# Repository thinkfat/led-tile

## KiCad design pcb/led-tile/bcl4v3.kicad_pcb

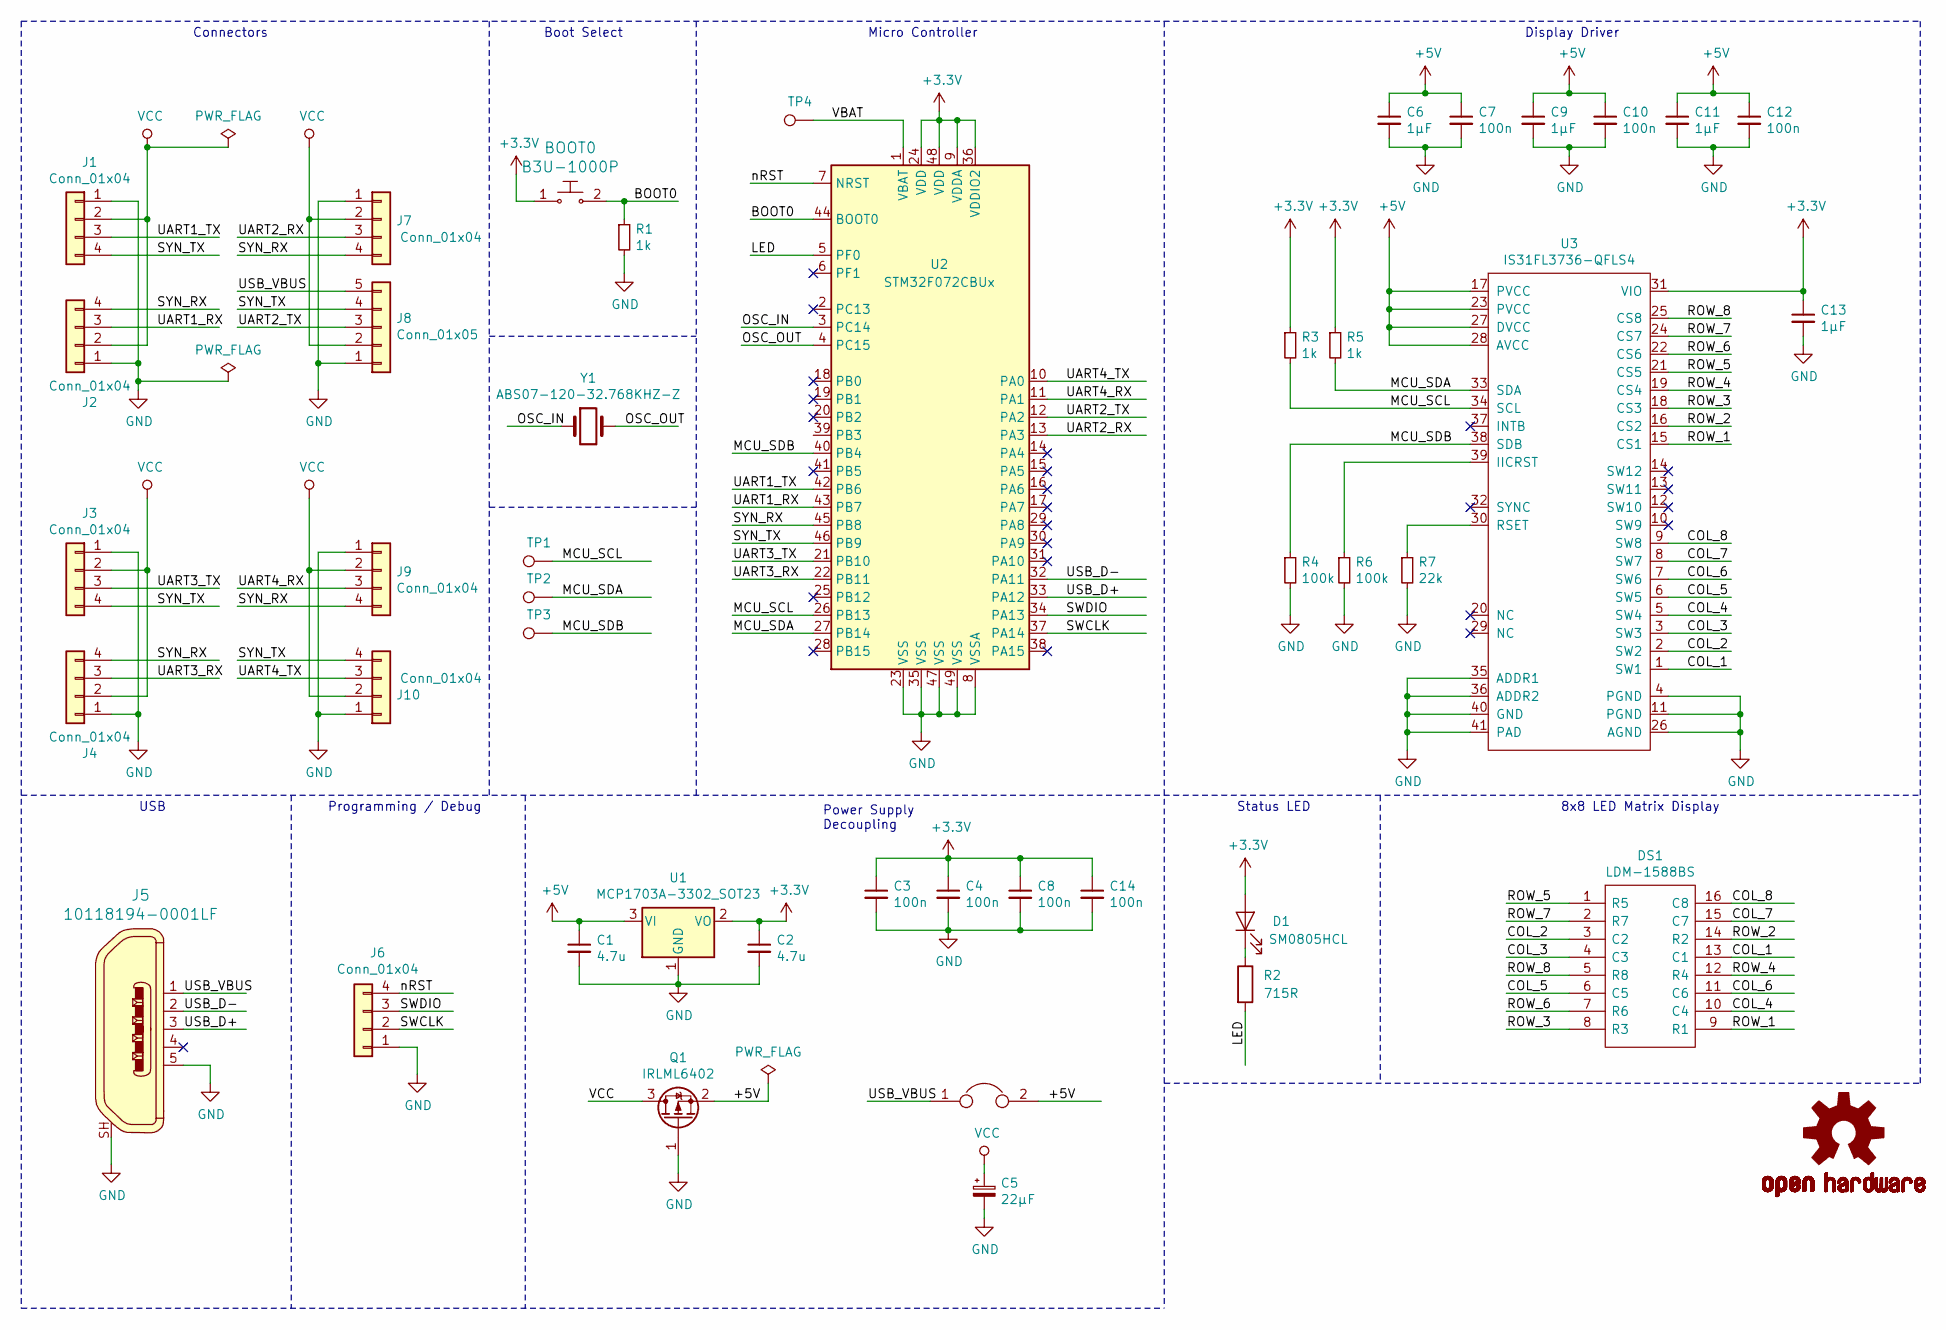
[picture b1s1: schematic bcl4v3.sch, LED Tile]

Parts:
BOOT0: B3U-1000P; Switch_Tactile_SMD_B3U-1000P; MPN B3U-1000P; Digi-Key_PN SW1020CT-ND
C1, C2: 4.7u; C_0805_2012Metric_Pad1.15x1.40mm_HandSolder
C3, C4, C7, C8, C10, C12, C14: 100n; C_0805_2012Metric_Pad1.15x1.40mm_HandSolder
C5: 22µF; CP_EIA-3528-15_AVX-H_Pad1.50x2.35mm_HandSolder
C6, C9, C11, C13: 1µF; C_0805_2012Metric_Pad1.15x1.40mm_HandSolder
D1: SM0805HCL; LED_0805_2012Metric_Castellated
DS1: LDM-1588BS; DIPS2794W50P254L3800H1065Q16N; Manufacturer_Part_Number TC15-11SRWA
J1, J2, J3, J4, J6, J7, J9, J10: Conn_01x04; PinHeader_1x04_P2.54mm_Vertical
J5: 10118194-0001LF; USB_Micro_B_Female_10118194-0001LF; MPN 10118194-0001LF; Digi-Key_PN 609-4618-1-ND
J8: Conn_01x05; PinHeader_1x05_P2.54mm_Vertical
JP1: Jumper; SMT-JUMPER_2_NC_TRACE_NO-SILK
LOGO1: OSHW-LOGOM; OSHW-LOGO-M
Q1: IRLML6402; SOT-23
R1, R3, R5: 1k; R_0805_2012Metric_Pad1.15x1.40mm_HandSolder
R2: 715R; R_0805_2012Metric_Pad1.15x1.40mm_HandSolder
R4, R6: 100k; R_0805_2012Metric_Pad1.15x1.40mm_HandSolder
R7: 22k; R_0805_2012Metric_Pad1.15x1.40mm_HandSolder
TP1, TP2, TP3, TP4: TestPoint; TestPoint_THTPad_1.0x1.0mm_Drill0.5mm
U1: MCP1703A-3302_SOT23; SOT-23
U2: STM32F072CBUx; QFN-48-1EP_7x7mm_P0.5mm_EP5.6x5.6mm
U3: IS31FL3736-QFLS4; QFN-40_EP_5x5_Pitch0.4mm
Y1: ABS07-120-32.768KHZ-Z; Crystal_SMD_MicroCrystal_CC7V-T1A-2Pin_3.2x1.5mm

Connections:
+3V3: BOOT0.1, C2.1, C3.1, C4.1, C8.1, C13.1, C14.1, D1.2 (A), R3.1, R5.1, U1.2 (VO), U2.9 (VDDA), U2.24 (VDD), U2.36 (VDDIO2), U2.48 (VDD), U3.31 (VIO)
+5V: C1.1, C6.1, C7.1, C9.1, C10.1, C11.1, C12.1, JP1.2, Q1.2 (S), U1.3 (VI), U3.17 (PVCC), U3.23 (PVCC), U3.27 (DVCC), U3.28 (AVCC)
/BOOT0: BOOT0.2, R1.1, U2.44 (BOOT0)
/COL_1: DS1.13 (C1), U3.1 (SW1)
/COL_2: DS1.3 (C2), U3.2 (SW2)
/COL_3: DS1.4 (C3), U3.3 (SW3)
/COL_4: DS1.10 (C4), U3.5 (SW4)
/COL_5: DS1.6 (C5), U3.6 (SW5)
/COL_6: DS1.11 (C6), U3.7 (SW6)
/COL_7: DS1.15 (C7), U3.8 (SW7)
/COL_8: DS1.16 (C8), U3.9 (SW8)
/LED: R2.2, U2.5 (PF0)
/MCU_SCL: R3.2, TP1.1, U2.26 (PB13), U3.34 (SCL)
/MCU_SDA: R5.2, TP2.1, U2.27 (PB14), U3.33 (SDA)
/MCU_SDB: R4.1, TP3.1, U2.40 (PB4), U3.38 (SDB)
/OSC_IN: U2.3 (PC14), Y1.1
/OSC_OUT: U2.4 (PC15), Y1.2
/ROW_1: DS1.9 (R1), U3.15 (CS1)
/ROW_2: DS1.14 (R2), U3.16 (CS2)
/ROW_3: DS1.8 (R3), U3.18 (CS3)
/ROW_4: DS1.12 (R4), U3.19 (CS4)
/ROW_5: DS1.1 (R5), U3.21 (CS5)
/ROW_6: DS1.7 (R6), U3.22 (CS6)
/ROW_7: DS1.2 (R7), U3.24 (CS7)
/ROW_8: DS1.5 (R8), U3.25 (CS8)
/SWCLK: J6.2, U2.37 (PA14)
/SWDIO: J6.3, U2.34 (PA13)
/SYN_RX: J2.4, J4.4, J7.4, J9.4, U2.45 (PB8)
/SYN_TX: J1.4, J3.4, J8.4, J10.4, U2.46 (PB9)
/UART1_RX: J2.3, U2.43 (PB7)
/UART1_TX: J1.3, U2.42 (PB6)
/UART2_RX: J7.3, U2.13 (PA3)
/UART2_TX: J8.3, U2.12 (PA2)
/UART3_RX: J4.3, U2.22 (PB11)
/UART3_TX: J3.3, U2.21 (PB10)
/UART4_RX: J9.3, U2.11 (PA1)
/UART4_TX: J10.3, U2.10 (PA0)
/USB_D+: J5.3, U2.33 (PA12)
/USB_D-: J5.2, U2.32 (PA11)
/USB_VBUS: J5.1, J8.5, JP1.1
/VBAT: TP4.1, U2.1 (VBAT)
/nRST: J6.4, U2.7 (NRST)
GND: C1.2, C2.2, C3.2, C4.2, C5.2, C6.2, C7.2, C8.2, C9.2, C10.2, C11.2, C12.2, C13.2, C14.2, J1.1, J2.1, J3.1, J4.1, J5.5, J5.SH, J6.1, J7.1, J8.1, J9.1, J10.1, Q1.1 (G), R1.2, R4.2, R6.2, R7.2, U1.1 (GND), U2.8 (VSSA), U2.23 (VSS), U2.35 (VSS), U2.47 (VSS), U2.49 (VSS), U3.4 (PGND), U3.11 (PGND), U3.26 (AGND), U3.35 (ADDR1), U3.36 (ADDR2), U3.40 (GND), U3.41 (PAD)
unnamed: D1.1 (K), R2.1
unnamed: R6.1, U3.39 (IICRST)
unnamed: R7.1, U3.30 (RSET)
VCC: C5.1, J1.2, J2.2, J3.2, J4.2, J7.2, J8.2, J9.2, J10.2, Q1.3 (D)

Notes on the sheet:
8x8 LED Matrix Display
Status LED
Micro Controller
Power Supply Decoupling
Boot Select
Connectors
USB
Programming / Debug
Display Driver

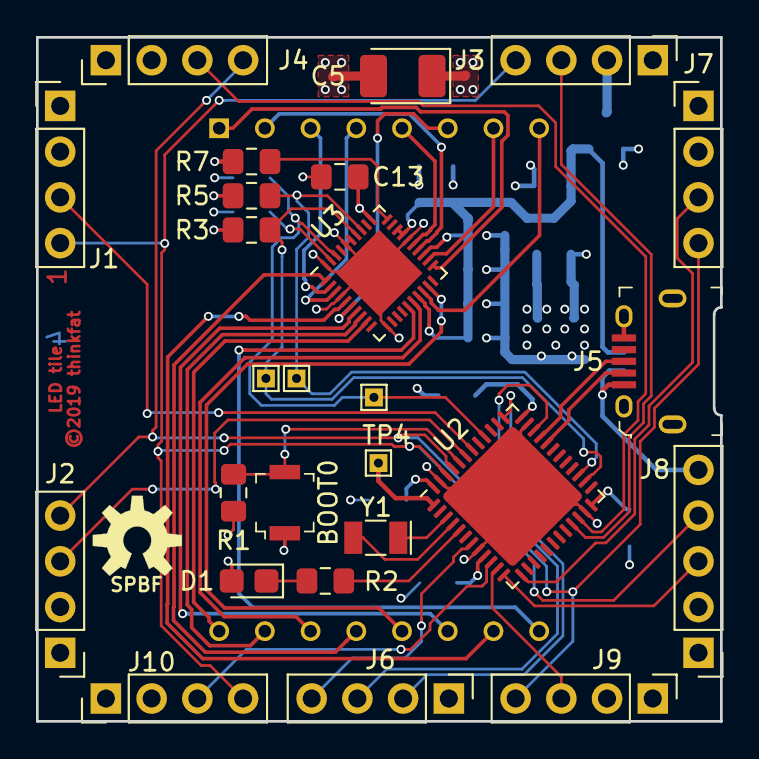
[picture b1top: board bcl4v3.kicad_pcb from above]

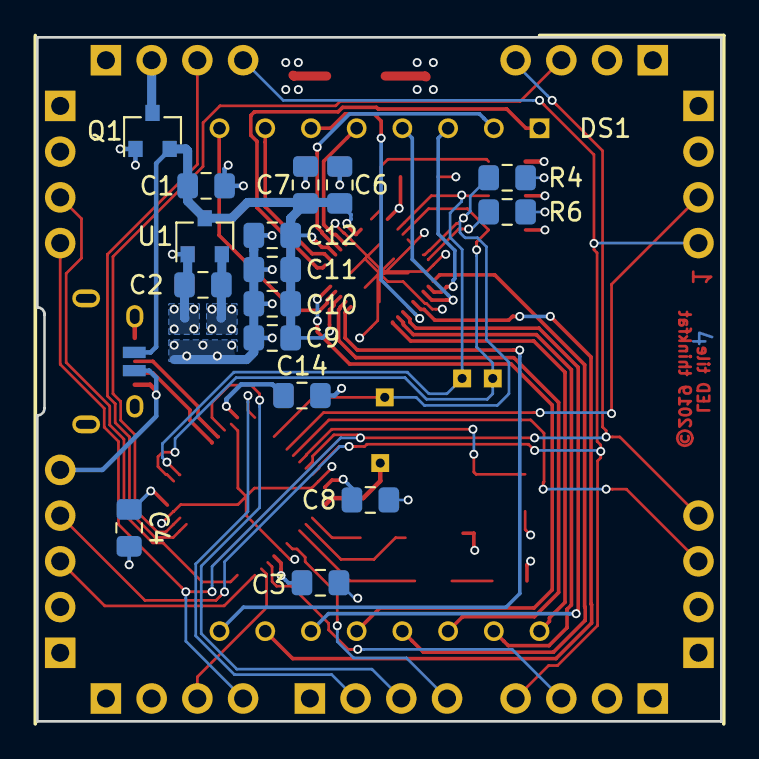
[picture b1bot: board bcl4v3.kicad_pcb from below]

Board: 4 copper layers, 38.0 x 38.0 mm, 45 parts (18 on the bottom side), 47 nets.

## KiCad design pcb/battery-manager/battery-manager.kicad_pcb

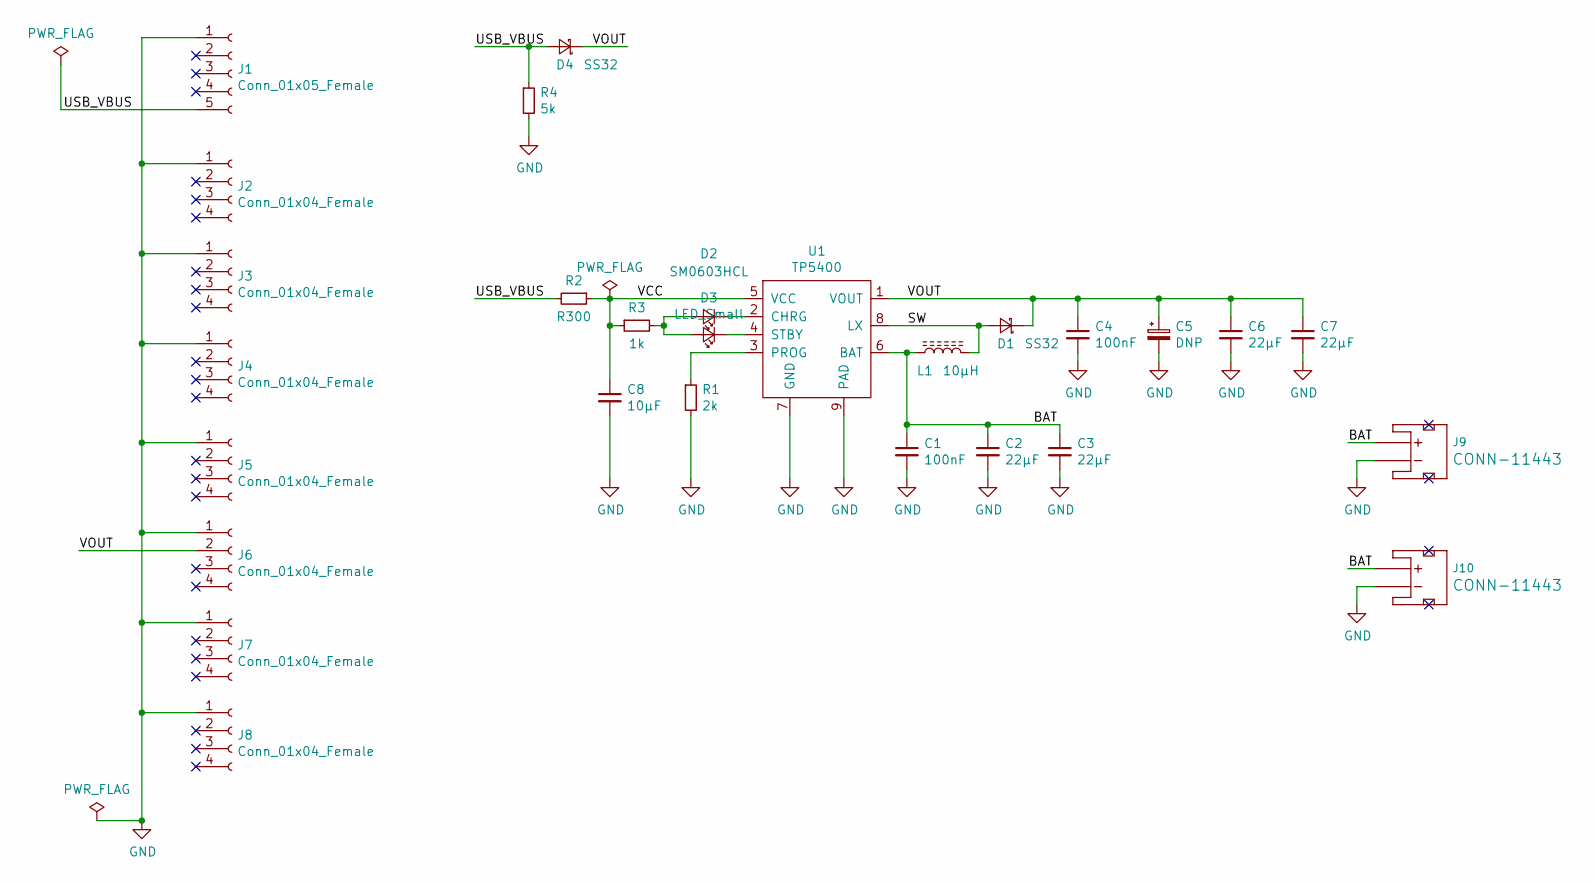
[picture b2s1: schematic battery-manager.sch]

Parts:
C1, C4: 100nF; C_0805_2012Metric
C2, C3, C6, C7: 22µF; C_1206_3216Metric
C5: DNP; CP_Elec_5x5.7
C8: 10µF; C_1206_3216Metric
D1, D4: SS32; D_SMA
D2: SM0603HCL; LED_0603_1608Metric_Castellated
D3: LED_Small; LED_0603_1608Metric_Castellated
J1: Conn_01x05_Female; PinSocket_1x05_P2.54mm_Vertical
J2, J3, J4, J5, J6, J7, J8: Conn_01x04_Female; PinSocket_1x04_P2.54mm_Vertical
J9, J10: JST_2MM_MALE; JST-2-SMD
L1: 10µH; L_Taiyo-Yuden_NR-40xx
R1: 2k; R_0805_2012Metric
R2: R300; R_1206_3216Metric
R3: 1k; R_0805_2012Metric
R4: 5k; R_0805_2012Metric
U1: TP5400; SOIC-8-1EP_3.9x4.9mm_P1.27mm_EP2.35x2.35mm

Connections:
/BAT: C1.1, C2.1, C3.1, J9.2 (+), J10.2 (+), L1.2, U1.6 (BAT)
/SW: D1.2 (A), L1.1, U1.8 (LX)
/USB_VBUS: D4.2 (A), J1.5, R2.2, R4.1
/VCC: C8.1, R2.1, R3.1, U1.5 (VCC)
/VOUT: C4.1, C5.1, C6.1, C7.1, D1.1 (K), D4.1 (K), J6.2, U1.1 (VOUT)
GND: C1.2, C2.2, C3.2, C4.2, C5.2, C6.2, C7.2, C8.2, J1.1, J2.1, J3.1, J4.1, J5.1, J6.1, J7.1, J8.1, J9.1 (-), J10.1 (-), R1.2, R4.2, U1.7 (GND), U1.9 (PAD)
unnamed: D2.1 (K), U1.2 (CHRG)
unnamed: D2.2 (A), D3.2 (A), R3.2
unnamed: D3.1 (K), U1.4 (STBY)
unnamed: R1.1, U1.3 (PROG)

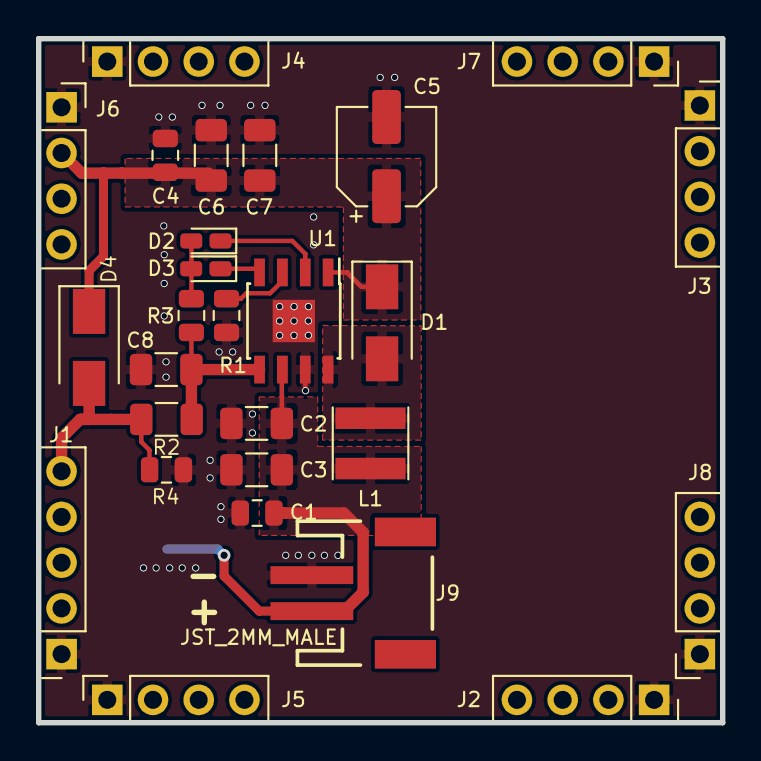
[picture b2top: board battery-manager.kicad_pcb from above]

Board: 2 copper layers, 38.0 x 38.0 mm, 28 parts (1 on the bottom side), 10 nets.

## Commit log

2019-03-02 - add some demos sketches without much of cleaning
2019-03-02 Add libopencm3 as a submodule
    to make compilation easier, add a suitable version of libopencm3 as a
    submodule to the project
2019-03-02 Initial commit - use the CERN OHL v1.2
2019-03-02 PCB and schematics updates
    - exchange STM32F070 with STM32F072 (USB w/o HSE)
    - remove xtal and related components
    - add boot mode jumper pads (NO)
    - connect USB_VBUS with VCC via jumper (NC)
    - smaller clearance for pad to solder mask
    - add local library directory for externally imported
2019-03-02 38x38mm matrix with DMA
    initial version, almost completely routed, i2c interface missing
2019-03-02 Board update
    fully routed PCB
    indicator LED added
2019-03-02 - add missing header, more cleanup
2019-03-02 - make hw config selectable during compile time
2019-03-02 - more cleanup and defining hw conf by macros
2019-03-02 PCB updates for panelization
    - place USB receptacle and edge cut-out smack center of the right board edge
    - rounded cut-out (.4mm radius) to allow routing it out using a single
    0.8mm wide slot.
2019-03-02 - switch to next hw revision
2019-03-02 - add prg_usb target
2019-03-02 PCB and schematics cleanup
    resize PCB to exactly 38x38mm, center the LED matrix
    add OSHW logo to silk screen, add copyright information
2019-03-02 - move the hardware definitions to one file
2019-03-02 correct dependency for "prg" target
    oocd programming only needs the ELF file
    also, use the preset OOCD variable to start openocd
2019-03-02 make life less boring
    - fix rule computation, cell death must be instant, but life may have
    shades of red
    - add a few heuristics to catch stagnant (boring) populations
2019-03-02 Makefile: provide TOPDIR variable
    useful to address OPENCM3 relative to the project root.
2019-03-02 prg: use the "program" macro to flash the target
    canonical method to flash a target is:
    "program ELF.elf verify reset exit"
    which takes care of everything. ELF file must be linked for the correct
    address in flash.
2019-03-02 Support for 38x38 v3 tile with DMA
    Lots of changes in this one
    - display scan-out with DMA
    - remove generic timer interrupts
    - PRNG with xorshift32
    - overall clean-up, removing lots of dead and ifdef'd code,
    formatting cleanup
2019-03-02 Fix reverse voltage protection, cleanups
    - power from USB doesn't need to go through protection FET
    - power to 3.3V LDO _must_ got through protection FET
    - add OSHW logo also to schematics so that it doesn't vanish if you
    sync PCB and schematics
    - modify copyright info a bit
2019-03-02 plot grayscales a bit faster
2019-03-02 Add test points, small routing changes
    - add test points for SPI bus
    - add net classes for VCC and LED networks
    - small routing changes
2019-03-02 small pcb fixes
    move USB_VBUS via out from under the USB receptacle (ouch)
    it just makes handsoldering difficult because the shield of
    the receptacle sucks up superfluous tin and then shorts
    USB_VBUS to ground
2019-03-02 refactor usart_buffered.c
    - move common isr code into single function
    - simplify ring buffer operations, make them easier to understand
2019-03-02 usart: new method for USART assignment to edge
    USARTS are now internally enumerated from A to D and their
    base pointers are stored in an array indexed from 0 to 3.
    Assignment of edges to USARTS is through symbolic name
    USART_[A-D]. usart_init() needs to be called in order
    A to D to match ISR assignments of rx/tx buffers.
    Also some cleanups and removal of dead/commented code.
2019-03-02 Correct display orientation to make (0,0) top left
    hardware should be reflected in the software.
2019-03-02 Cleanup main()
    add cpu_relax() inline function to execute "wfi" in the main loop
    general cleanup
2019-03-02 Cleanup usart_buffered API, add usart_buf_clear()
2019-03-02 life: first connected version
    add sync protocol via GPIO so that all tiles are working
    simultaneously. add transmit/receive of edge states to and
    from adjacent tiles.
2019-03-02 Add CDCACM USB function
    Serial line for debug and control
2019-03-02 disp: add fast version of disp_set
    add disp_set_noupdate() which only sets the display buffer
    but doesn't update the DMA row buffer. Useful for bulk
    updates of the display that touch all rows multiple times.
    also add disp_update_rows() to update all DMA row buffers
    at once.
2019-03-02 work around pcb bug to keep tile in sync
    still not completely OK, though.
2019-03-02 life: update interpretation of S23/B36 rule
    cells are born with 3 and 6 neighbors and also survive with 6 neighbors
    not sure if this is correct but the results seem to be OK.
2019-03-02 life: fix life tick updates
    compute life tick through a multiplier and update the multiplier
    once every tick based on console input
2019-03-02 Sync GPIO corrections, add tactile switch for BOOT0 signal
2019-03-02 Add simple serial console over CDCACM
    add the following functions:
    - console_printf (warning, adds a lot of library code!)
    - console_putc
    - console_puts
    - console_getc
2019-03-02 life: switch trace output to the console layer
2019-03-02 console: console_printf made configurable
    can be left out of the build to save flash space
2019-03-02 life: major update
    - new protocol for edge updates to create a namespace for control messages
    - fix major bug in tile sync protocol, sync is now realiable
    - add output of trace information through cdcacm function
    - depending on which edges are adjacent to each other, state messaages
    from the neighboring tiles need to be reversed to match coordinate
    systems
2019-03-02 usart_buffered: enable pull-ups on RX lines
    try to prevent spurious inputs on unconnected USART RX lines
2019-03-02 PCB updates: 32kHz oscillator, separate VBAT supply
    also, longer pads for the row driver
2019-03-02 wordclock: small corrections
    "A QUARTER" instead of "QUARTER"
    remove an "unused function" warning
    remove a debug print
2019-03-02 make: add rtc and wordclock to compile
2019-03-02 introduce "applet" mini-framework
    Minimal framework for "applets" running from the main loop. A
    new "struct applet" keeps pointers to an "init" and a "worker" function.
    A "struct applet" instance can be registered with the framework by the
    macro "applet_add", which puts an instance pointer into a dedicated ELF
    section. Two functions applet_init_all() and applet_run_all() are then
    called from main() to run the init and worker functions. This removes
2019-03-02 rtc: rtc initialization and time-set over cdcacm
2019-03-02 cdcacm: initialize buffers on init
2019-03-02 add udev hotplug rule
    to set the wordclock when connected
2019-03-02 wordclock: simple wordclock app
    "FIVE TO NINE"
2019-03-02 main: run wordclock instead of life app
2019-03-02 pcb: put USB_VBUS to pin header
    Replace one pin header with a 5-contact version and route USB_VBUS
    to this pin. Necessary to power a plug-on battery shield from the main
    USB connector.
2019-03-02 pcb: add battery shield
    based on a TP5400 single-chip LiPo powerbank solution
2019-03-02 pcb: add 3d model for ABS07 crystal resonator
2019-03-03 firmware: fix display gpio initialization
    RCC clock defines cannot be OR'd together.
2019-03-03 applet'ify usart_buffered
    also increases the buffer size to 16
2019-03-03 firmware: make led_init static
2019-03-03 firmware: compile usart code only with life applet
    not needed for other applets right now
2019-03-03 firmware: remove hardcoded interface definition from openocd config
2019-03-03 firmware: allow seconds-precision when setting the clock
    also adjust udev rule
2019-03-04 pcb: add archive of used footprints
    make sure pcb can be opened even if footprint libraries are missing
2019-03-24 pcb: update battery shield pcb to latest version
    mainly, add a power path to supply the target with power when the
    TP5400 is charging the battery, as in this mode the boost converter is
    not active and the target is supplied with the current battery voltage
2019-03-24 pcb: add fabrication files
    gerber and drill file for current pcb.
2019-03-24 pcb: update led-tile to latest version
    move OSHW logo into a project specific library as not everyone has the
    Sparkfun Libraries installed, decrease current through the SMD LED,
2019-03-24 fw: use objcopy from $(PREFIX)
    use $(PREFIX)-objcopy when converting the target ELF file to binary
2019-03-24 fw: remove obsoleted files
    not needed any more
2019-03-24 fw: reduce multiplexing frequency of matrix display
    be slower to save a bit of power
2019-03-24 fw: make sure RTC is initialized to 24h mode
    this should be the power-on default, but better be sure.
2019-03-24 fw: reduce wordclock brightness between 23h and 7h
    make it so that the display is less bright during night hours when the
    clock is on your bedside table.
2019-04-05 pcb: use IS31FL3730 as matrix driver
    reduce component count
2019-05-31 Variant of the tile with integrated LED matrix driver
    Use ISSI IS31FL3736 instead of discrete ICs for driving the
    LED matrix
2019-05-31 pcb: add wordmask pcb
    instead of a sheet of paper, use a thin piece of PCB as a wordmask
    for the word clock
2019-05-31 fw: display driver for IS31FL3736

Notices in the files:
pcb/led-tile/bcl4v3.kicad_pcb:
©2019 thinkfat
